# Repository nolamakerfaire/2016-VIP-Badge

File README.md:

# 2016 VIP Badge

The 2016 New Orleans Mini Maker Faire VIP Badge features an integrated 3.3v 8Mhz Arduino Pro Mini derivative microcontroller and USB FTDI Programmer. The badges come pre-assembled, and feature breakout headers to access the digital and analog pins as well as ground and voltage. Any 3.3v-compatible components can be used with the badge. Additionally, battery packs will be included, but they badge can also be powered by a standard USB cellphone charging battery. Finally, the Arduino Pro Mini derivative and the USB programmer snap out of the badge so you can easily integrate them into future projects.

The badge can be programmed just like a standard [Arduino Pro Mini](https://www.arduino.cc/en/Guide/ArduinoProMini). In the Arduino IDE, select Arduino Pro or Pro Mini (3.3V, 8 MHz) w/ ATmega328 from the Tools > Board menu. 

[Check out our wiki](https://github.com/nolamakerfaire/2016-VIP-Badge/wiki) for some tips on using this board.

Here's a great guide to getting started with the Arduino Pro Mini: [https://learn.sparkfun.com/tutorials/using-the-arduino-pro-mini-33v](https://learn.sparkfun.com/tutorials/using-the-arduino-pro-mini-33v)

If snapped apart, you can solder pin headers onto the USB programmer and use it exactly like the [Sparkfun FTDI Basic Breakout Board](https://www.sparkfun.com/products/9873).

## License Information

The Arduino Pro Mini derivative hardware is released under [Creative Commons Share-alike 3.0](http://creativecommons.org/licenses/by-sa/3.0/).

The FTDI Basic Breakout derivative hardware is released under [Creative Commons ShareAlike 4.0 International](https://creativecommons.org/licenses/by-sa/4.0/).

**Hardware authors:**
- Original Arduino Mini design by Team Arduino. Pro Mini design by Nathan Seidle @ SparkFun Electronics; revision work by Pete Lewis @ SparkFun Electronics
- Original FTDI Basic Breakout design by [Sparkfun](https://www.sparkfun.com/products/9873).
- 2016 VIP Badge hardware design by Scott Thomas.

Distributed as-is; no warranty is given.

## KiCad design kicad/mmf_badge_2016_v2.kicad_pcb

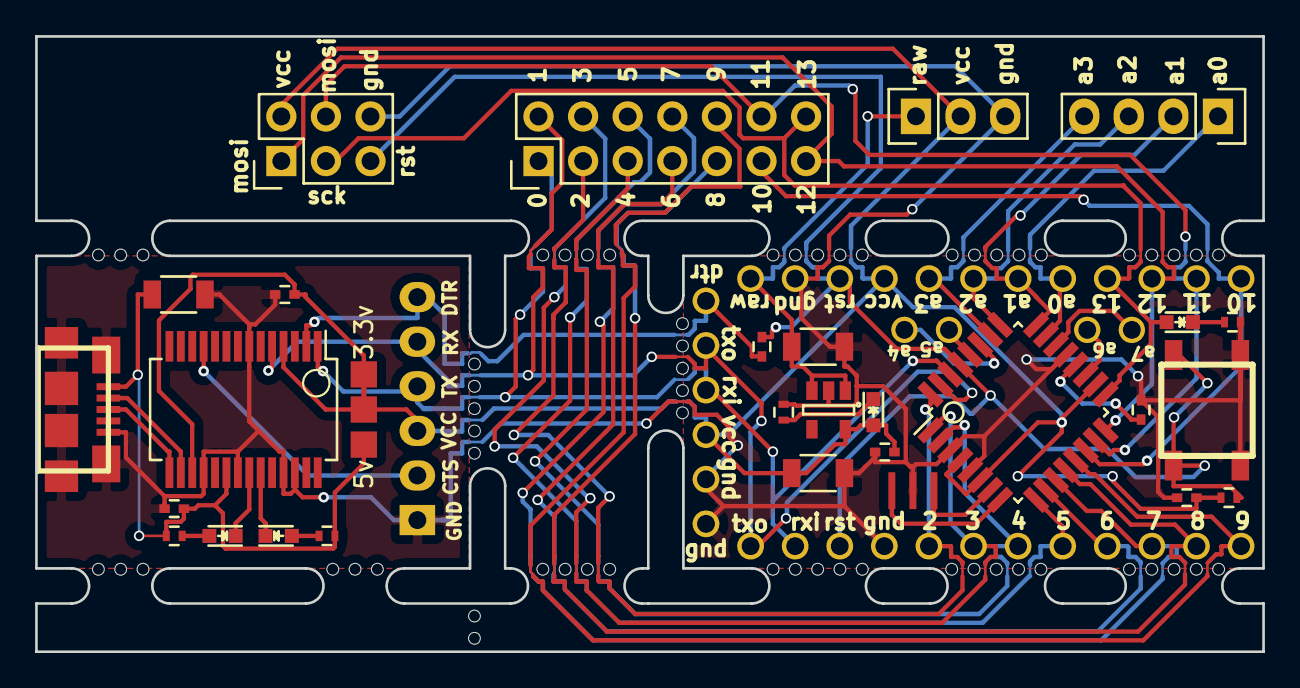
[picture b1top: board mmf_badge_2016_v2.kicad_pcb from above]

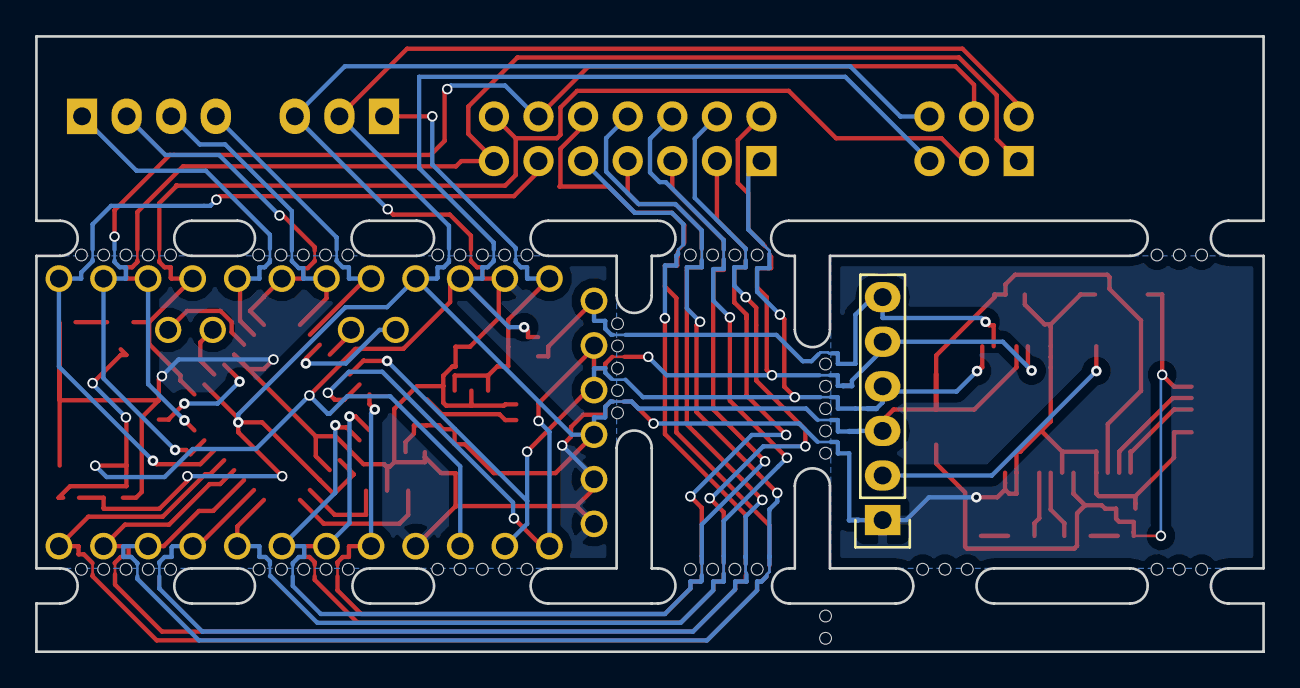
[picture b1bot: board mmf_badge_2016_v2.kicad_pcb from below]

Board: 2 copper layers, 69.9 x 35.1 mm, 35 parts (5 on the bottom side), 45 nets.

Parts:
C1, C2, C3, C4, C6, C10: 0.1uF; C_0402
C5, C13, C19: 10uF; C_1206
LED1: Red; LED-0603
LED2: Green; LED-0603
LED3: GREEN; LED-0603
LED4: RED; LED-0603
P1: MICRO_USB_B; USB_Micro-B_SMD
P2: CONN_01X06; Pin_Header_Straight_1x06
P3: ARDUPROMINI; ArduProMini
P4: CONN_02X03; Pin_Header_Straight_2x03
P5: CONN_01X03; Pin_Header_Straight_1x03
P6: CONN_01X04; Pin_Header_Straight_1x04
P7: CONN_02X07; Pin_Header_Straight_2x07
Q1: Resonator; SMD_Resonator
R2, R11: 10k; R_0402
R5, R7: 1K; R_0402
R6: 330; R_0402
S1: Reset; SW_SPST_EVPBF
SL1: Solder_Link
U1: ATMEGA328P-A; TQFP-32_7x7mm_Pitch0.8mm
U2: MIC5205; SOT-23-5
U3: FT232RLSSOP; SSOP-28_5.3x10.2mm_Pitch0.65mm
nt1, nt2, nt3, nt4: Net-tie; Net_tie

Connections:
+3V3: C4.1, SL1.2, U3.17
+5V: C5.1, C6.1, P1.1, R5.1, R7.1, SL1.3, U3.20
/A0: P3.26, P6.1, U1.23
/A1: P3.25, P6.2, U1.24
/A2: P3.24, P6.3, U1.25
/A3: P3.23, P6.4, U1.26
/A4: P3.31, U1.27
/A5: P3.32, U1.28
/A6: P3.34, U1.19
/A7: P3.35, U1.22
/CTS: P2.2, U3.11
/D2: P3.11, P7.3, U1.32
/D3: P3.12, P7.4, U1.1
/D4: P3.13, P7.5, U1.2
/D5: P3.14, P7.6, U1.9
/D6: P3.15, P7.7, U1.10
/D7: P3.16, P7.8, U1.11
/D8: P3.17, P7.9, U1.12
/D9: P3.18, P7.10, U1.13
/D10: P3.30, P7.11, U1.14
/D+: P1.3, U3.15
/D-: P1.2, U3.16
/DTR: C2.2, P2.6, P3.6, U3.2
/GND: C1.2, C3.2, C10.2, C13.2, C19.2, P3.1, P3.2, P3.10, P3.20, P4.6, P5.3, Q1.2, R6.1, R11.1, S1.2, U1.3, U1.5, U1.21, U2.2, nt1.2
/GNDP: C4.2, C5.2, C6.2, P1.5, P2.1, U3.7, U3.18, U3.21, U3.25, U3.26, nt1.1
/MISO: P3.28, P4.1, P7.13, U1.16
/MOSI: P3.29, P4.4, P7.12, U1.15
/POWER: P2.3, SL1.1, U3.4, nt2.1
/RAW: C19.1, P3.19, P5.1, U2.1, U2.3
/RESET: C2.1, P3.9, P3.21, P4.5, R2.2, S1.1, U1.29
/RXI: P3.4, P3.8, P7.1, U1.30, nt3.1
/RXIP: P2.5, U3.5, nt4.2
/RXLED: LED4.1, U3.22
/SCK: LED2.2, P3.27, P4.3, P7.14, U1.17
/TXLED: LED3.1, U3.23
/TXO: P3.5, P3.7, P7.2, U1.31, nt4.1
/TXOP: P2.4, U3.1, nt3.2
/VCC: C3.1, C10.1, C13.1, LED1.2, P3.3, P3.22, P4.2, P5.2, R2.1, U1.4, U1.6, U1.18, U2.5, nt2.2
unnamed: C1.1, U1.20
unnamed: LED1.1, R11.2
unnamed: LED2.1, R6.2
unnamed: LED3.2, R5.2
unnamed: LED4.2, R7.2
unnamed: Q1.1, U1.8
unnamed: Q1.3, U1.7

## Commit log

2016-03-13 Cleaning up directory structure
2016-03-13 Added BoM
2016-03-28 Added tutorial link in readme
2016-04-10 Added wiki link
2016-04-10 Fixed wiki link
